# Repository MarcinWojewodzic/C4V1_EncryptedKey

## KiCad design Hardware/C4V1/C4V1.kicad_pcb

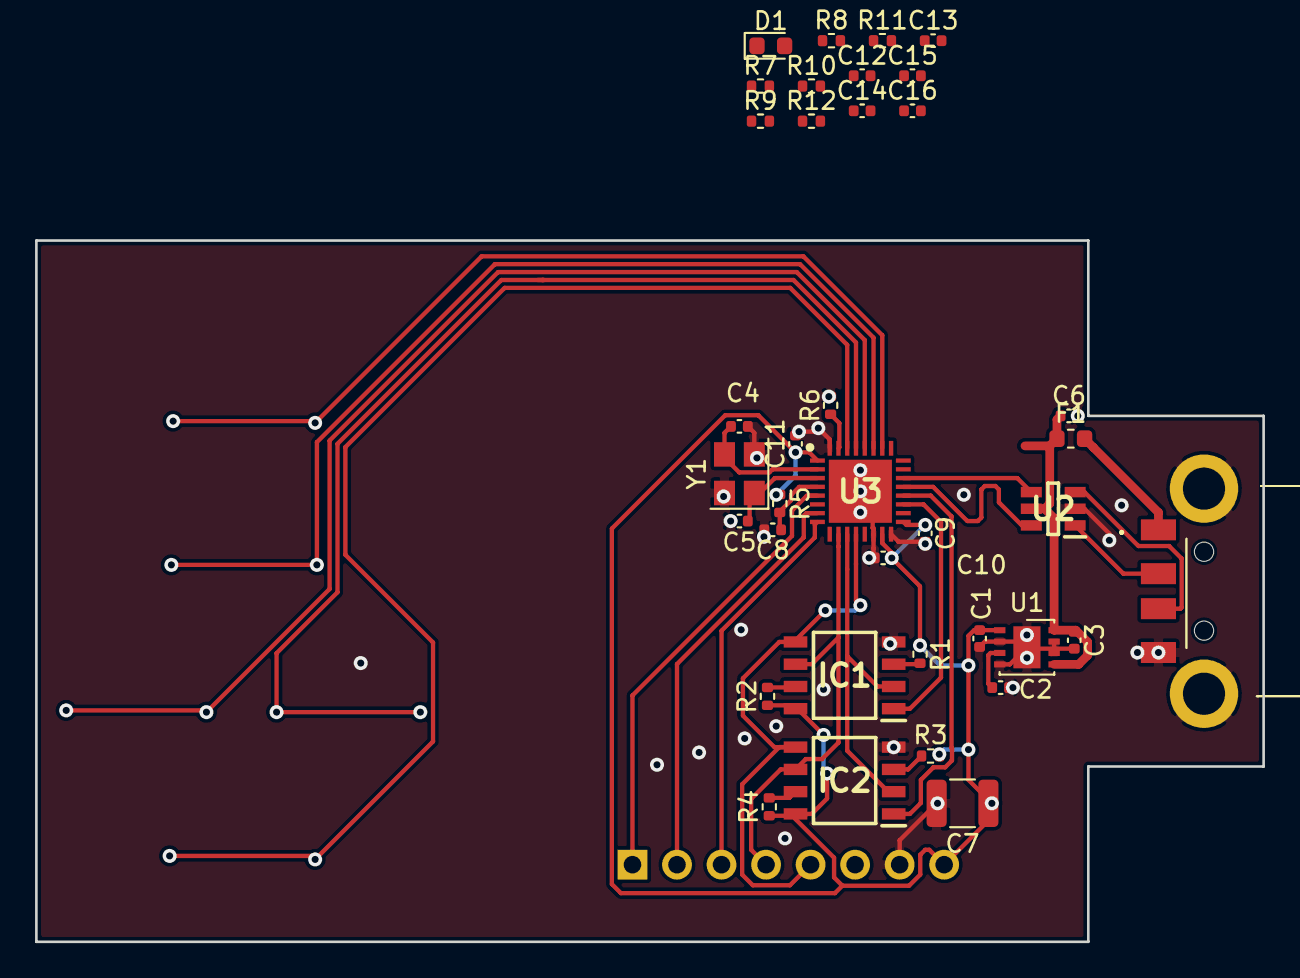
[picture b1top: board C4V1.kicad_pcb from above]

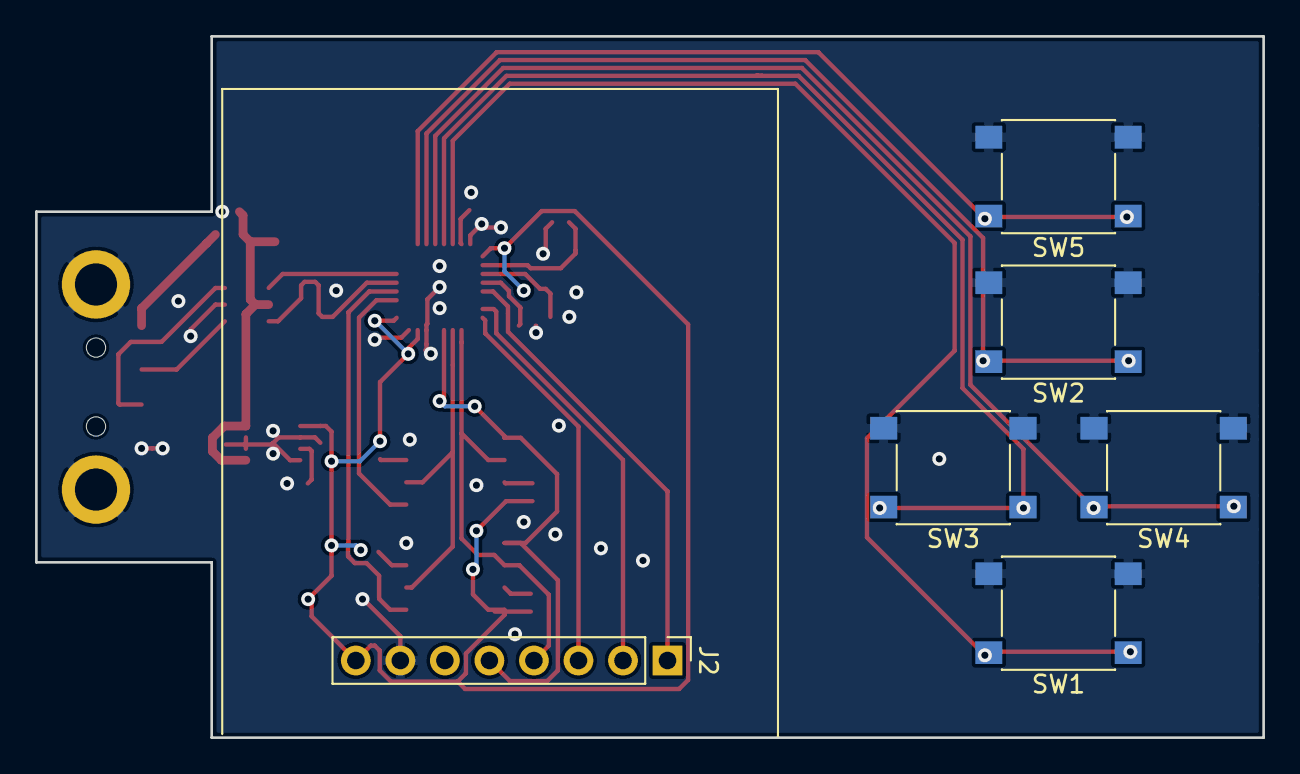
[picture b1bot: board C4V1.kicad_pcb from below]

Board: 2 copper layers, 70.0 x 40.0 mm, 43 parts (6 on the bottom side), 32 nets.

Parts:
C1, C3, C6, C9, C10, C11: 4.7u/X5R/10V; C_0402_1005Metric
C2: 10n/X5R/10V; C_0402_1005Metric
C4: 8p/C0G/10V; C_0402_1005Metric
C5: 8p/COG/10V; C_0402_1005Metric
C7: 100u/X7R/10V; C_1210_3225Metric
C8, C12, C13, C14, C15, C16: 100n/X5R/10V; C_0402_1005Metric
D1: LED; LED_0603_1608Metric
F1: SF-0603SA050M-2; Fuse_0603_1608Metric
IC1: W25Q16JVSNIQ; SOIC127P600X175-8N
IC2: MB85RS256TYPNF-G-AWERE2; SOIC127P600X175-8N
J1: 48037-2100; 480372100
J2: Conn_01x08_Male; PinHeader_1x08_P2.54mm_Vertical
R1, R2, R3, R4, R5, R6, R8, R9, R10, R11, R12: 10k/5%/0.1W; R_0402_1005Metric
R7: /5%/0.1W; R_0402_1005Metric
SW1, SW2, SW3, SW4, SW5: SW_Push; SW_Push_1P1T_NO_6x6mm_H9.5mm
U1: LDLN050PU33; DFN-8-1EP_3x3mm_P0.65mm_EP1.55x2.4mm
U2: ESDALCL6-2SC6; SOT95P280X145-6N
U3: STM32G4A1KEU6; QFN50P500X500X60-33N-D
Y1: ECS-80-8-33Q-ADS-TR3; Crystal_SMD_Abracon_ABM8G-4Pin_3.2x2.5mm

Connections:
+3V3: C1.1, C7.1, C9.1, C10.1, C11.1, IC1.8, IC2.8, J2.8, R1.1, R2.1, R3.1, R4.1, R5.1, U1.1, U3.1, U3.15, U3.17
CLK: IC1.6, IC2.6, J2.4, U3.10
D+: U2.4, U3.22
D-: U2.6, U3.21
DC: J2.2, U3.7
DOWN: C15.1, R11.2, SW2.1, U3.27
GND: C1.2, C2.2, C3.2, C4.1, C5.1, C6.2, C7.2, C8.2, C9.2, C10.2, C11.2, IC1.4, IC2.4, J1.4, J1.5, J2.7, R6.2, SW1.2, SW2.2, SW3.2, SW4.2, SW5.2, U1.2, U1.4, U1.6, U1.7, U1.9, U2.2, U3.14, U3.16, U3.32, U3.33, Y1.2, Y1.4
LEFT: C14.1, R10.2, SW3.1, U3.29
MISO: IC1.2, IC2.2, U3.11
MOSI: IC1.5, IC2.5, J2.5, U3.12
unnamed: C2.1, U1.3
unnamed: C4.2, U3.2, Y1.3
unnamed: C5.2, U3.3, Y1.1
unnamed: C8.1, R5.2, U3.4
unnamed: D1.2, R7.1
unnamed: F1.2, J1.1
unnamed: IC1.3, R1.2
unnamed: IC1.7, R2.2
unnamed: IC2.3, R3.2
unnamed: IC2.7, R4.2
unnamed: J1.2, U2.1
unnamed: J1.3, U2.3
unnamed: R6.1, U3.31
unnamed: R7.2, U3.25
OK: C12.1, R8.2, SW5.1, U3.26
RIGHT: C13.1, R9.2, SW4.1, U3.28
UP: C16.1, R12.2, SW1.1, U3.30
VBUS: C3.1, C6.1, F1.1, U1.5, U1.8, U2.5
~CS: J2.3, U3.8
~FLASH_CS: IC1.1, U3.19
~FRAM_CS: IC2.1, U3.20
~RES: J2.1, U3.5

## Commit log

2023-02-25 Wstępny schemat
2023-02-26 Prawie ukończona płytka
2023-03-03 Przedostatnie poprawki
2023-03-04 Dodano początkową konfiguracje
2023-04-23 Dodano początkowe struktury
2023-05-07 Dodano lepszą bibliotekę do Fram
